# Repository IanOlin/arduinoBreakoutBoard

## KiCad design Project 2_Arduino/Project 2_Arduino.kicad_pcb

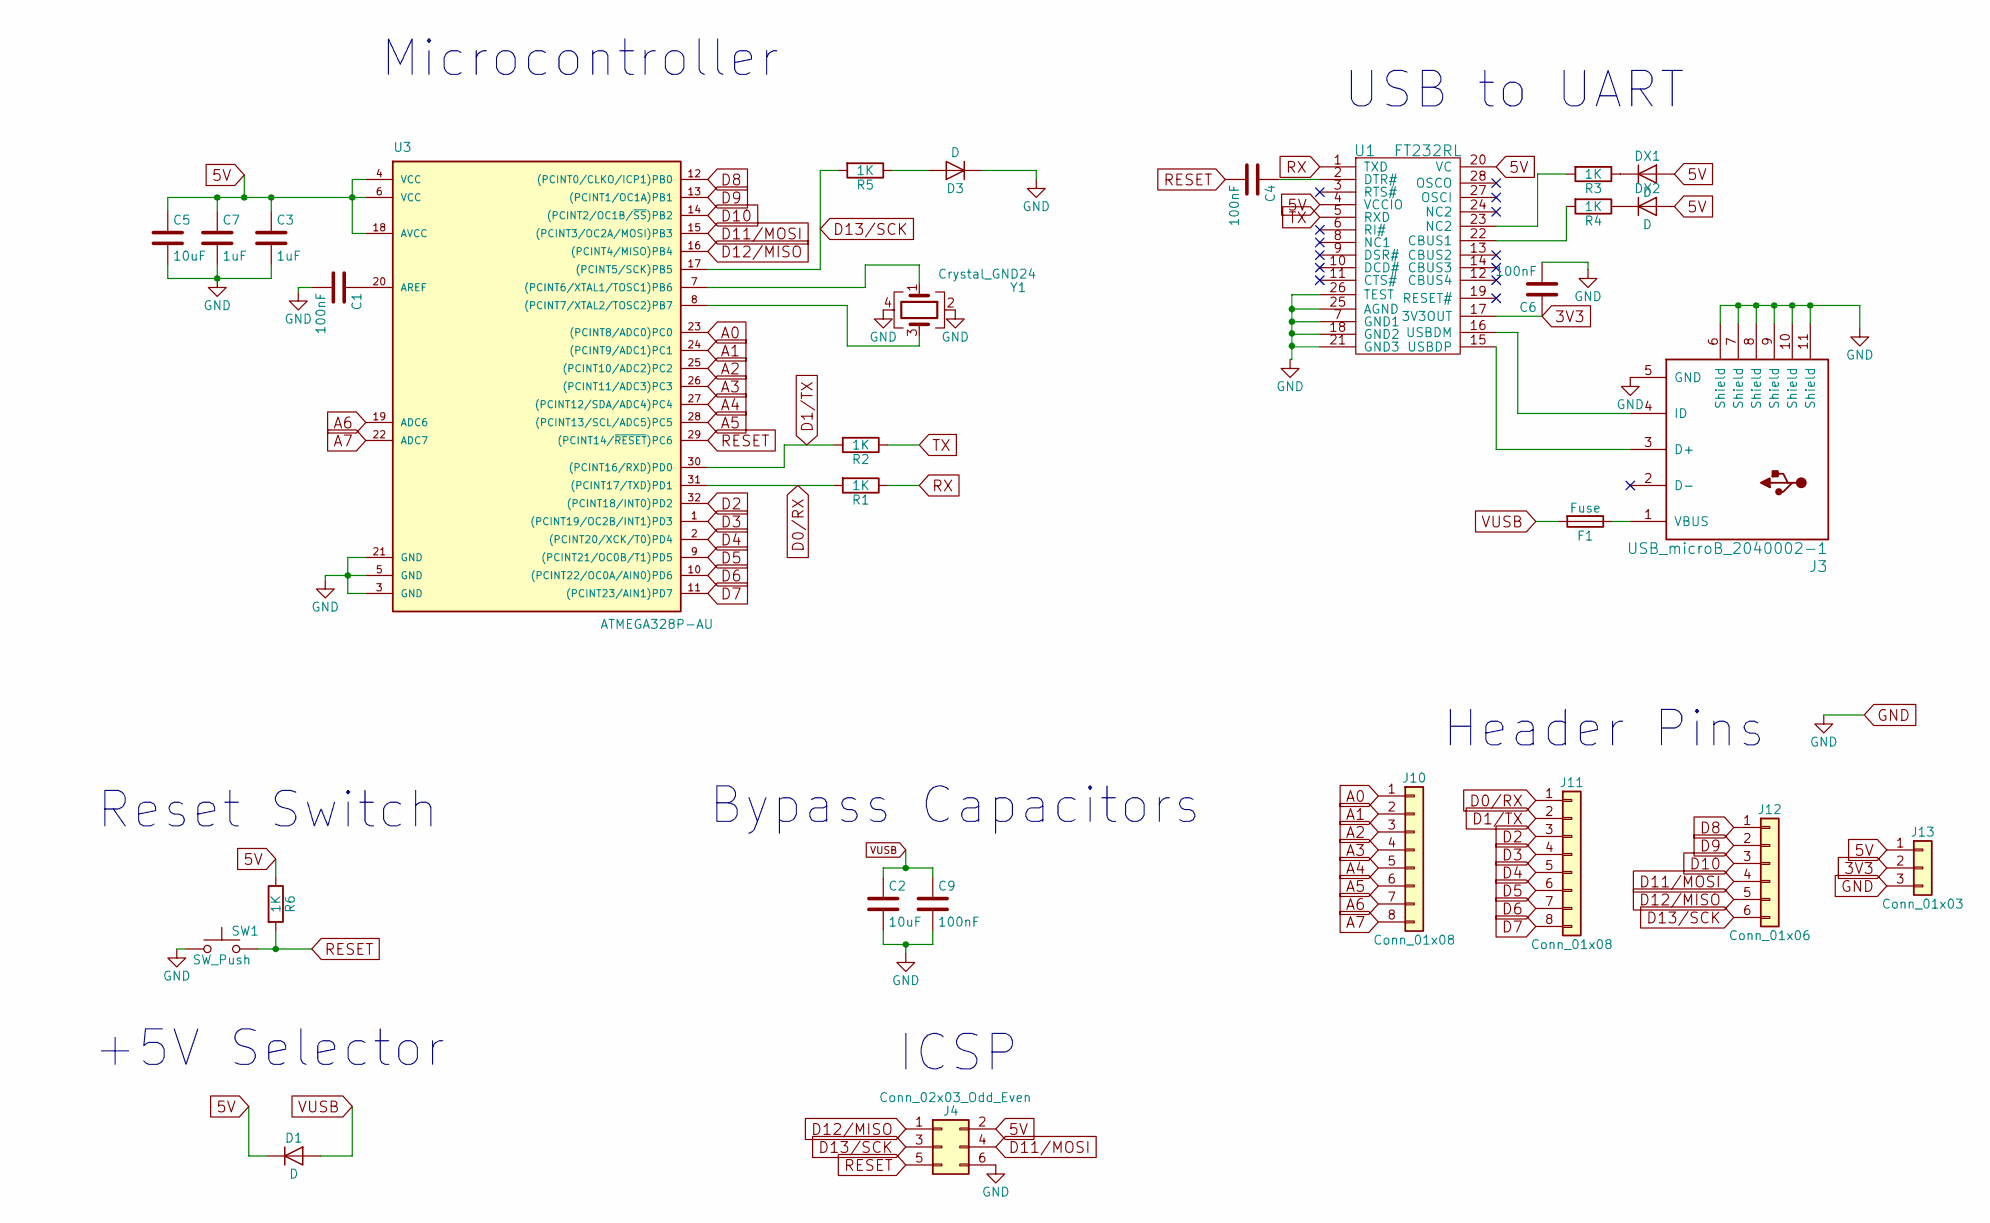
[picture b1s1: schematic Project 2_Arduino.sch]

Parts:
C1, C4, C6, C9: 100nF; C_0603
C2, C5: 10uF; C_0805
C3, C7: 1uF; C_0603
D1, D3: D; D_0805
DX1, DX2: D; D_0805
F1: Fuse; FuseSMD0603
J3: USB_microB_2040002-1
J4: Conn_02x03_Odd_Even; Pin_Header_Straight_2x03_Pitch1.00mm
J10, J11: Conn_01x08; Pin_Header_Straight_1x08_Pitch1.00mm
J12: Conn_01x06; Pin_Header_Straight_1x06_Pitch1.00mm
J13: Conn_01x03; Pin_Header_Straight_1x03_Pitch1.00mm
R1, R2, R3, R4, R5, R6: 1K; R_0603
SW1: SW_Push; SPSTbtn
U1: FT232RL; TQFP-32_7x7mm_Pitch0.8mm
U3: ATMEGA328P-AU; TQFP-32_7x7mm_Pitch0.8mm
Y1: Crystal_GND24

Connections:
3V3: C6.1, J13.2, U1.17 (3V3OUT)
5V: C3.1, C5.1, C7.1, D1.1 (K), DX1.2 (A), DX2.2 (A), J4.2, J13.1, R6.1, U1.4 (VCCIO), U1.20 (VC), U3.4 (VCC), U3.6 (VCC), U3.18 (AVCC)
A0: J10.1, U3.23 ((PCINT8/ADC0)PC0)
A1: J10.2, U3.24 ((PCINT9/ADC1)PC1)
A2: J10.3, U3.25 ((PCINT10/ADC2)PC2)
A3: J10.4, U3.26 ((PCINT11/ADC3)PC3)
A4: J10.5, U3.27 ((PCINT12/SDA/ADC4)PC4)
A5: J10.6, U3.28 ((PCINT13/SCL/ADC5)PC5)
A6: J10.7, U3.19 (ADC6)
A7: J10.8, U3.22 (ADC7)
D0/RX: J11.1, R1.2, U3.31 ((PCINT17/TXD)PD1)
D1/TX: J11.2, R2.2, U3.30 ((PCINT16/RXD)PD0)
D2: J11.3, U3.32 ((PCINT18/INT0)PD2)
D3: J11.4, U3.1 ((PCINT19/OC2B/INT1)PD3)
D4: J11.5, U3.2 ((PCINT20/XCK/T0)PD4)
D5: J11.6, U3.9 ((PCINT21/OC0B/T1)PD5)
D6: J11.7, U3.10 ((PCINT22/OC0A/AIN0)PD6)
D7: J11.8, U3.11 ((PCINT23/AIN1)PD7)
D8: J12.1, U3.12 ((PCINT0/CLKO/ICP1)PB0)
D9: J12.2, U3.13 ((PCINT1/OC1A)PB1)
D10: J12.3, U3.14 ((PCINT2/OC1B/~SS~)PB2)
D11/MOSI: J4.4, J12.4, U3.15 ((PCINT3/OC2A/MOSI)PB3)
D12/MISO: J4.1, J12.5, U3.16 ((PCINT4/MISO)PB4)
D13/SCK: J4.3, J12.6, R5.2, U3.17 ((PCINT5/SCK)PB5)
GND: C1.2, C2.2, C3.2, C5.2, C6.2, C7.2, C9.2, D3.1 (K), J3.5 (GND), J3.6 (Shield), J3.7 (Shield), J3.8 (Shield), J3.9 (Shield), J3.10 (Shield), J3.11 (Shield), J4.6, J13.3, SW1.1, U1.7 (GND1), U1.18 (GND2), U1.21 (GND3), U1.25 (AGND), U1.26 (TEST), U3.3 (GND), U3.5 (GND), U3.21 (GND), Y1.2, Y1.4
unnamed: C1.1, U3.20 (AREF)
unnamed: C4.1, U1.2 (DTR#)
unnamed: D3.2 (A), R5.1
unnamed: DX1.1 (K), R3.1
unnamed: DX2.1 (K), R4.1
unnamed: F1.1, J3.1 (VBUS)
unnamed: J3.3 (D+), U1.15 (USBDP)
unnamed: J3.4 (ID), U1.16 (USBDM)
unnamed: R3.2, U1.23 (NC2)
unnamed: R4.2, U1.22 (CBUS1)
unnamed: U3.7 ((PCINT6/XTAL1/TOSC1)PB6), Y1.1
unnamed: U3.8 ((PCINT7/XTAL2/TOSC2)PB7), Y1.3
RESET: C4.2, J4.5, R6.2, SW1.2, U3.29 ((PCINT14/~RESET~)PC6)
RX: R1.1, U1.1 (TXD)
TX: R2.1, U1.5 (RXD)
VUSB: C2.1, C9.1, D1.2 (A), F1.2

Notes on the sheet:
ICSP
+5V Selector
Reset Switch
Microcontroller
Header Pins
USB to UART
Bypass Capacitors

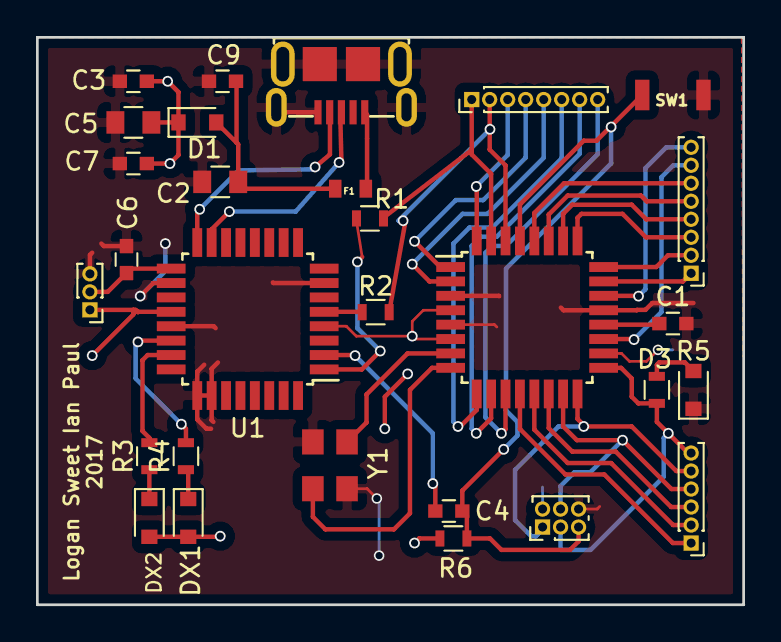
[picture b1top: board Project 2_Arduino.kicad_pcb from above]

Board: 2 copper layers, 39.2 x 31.5 mm, 29 parts (0 on the bottom side), 41 nets.

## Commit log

2017-10-12 libraries created
2017-10-12 schematics USB UART added
2017-10-12 added footprint library
2017-10-12 USB to UART done
2017-10-12 added brad's usb
2017-10-12 first pass schematic done
2017-10-12 rearrange
2017-10-12 finished footprints
2017-10-12 caps edited
2017-10-12 footprints associated
2017-10-12 git debacle 2
2017-10-12 new crystal
2017-10-12 new clock schematic
2017-10-12 finished layout
2017-10-12 fixed flows
2017-10-12 added BOM csv
2017-10-15 connections and USB location fixed
